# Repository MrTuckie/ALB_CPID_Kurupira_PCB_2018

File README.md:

# Kurupira-PCB
Descrição da PCB e dos componentes na PCB

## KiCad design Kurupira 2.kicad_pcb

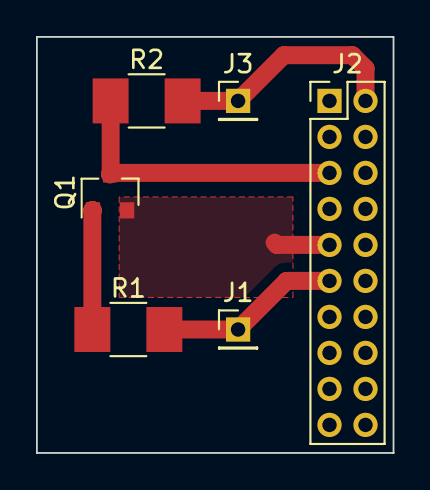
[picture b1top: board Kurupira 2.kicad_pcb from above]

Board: 2 copper layers, 19.8 x 23.1 mm, 6 parts (0 on the bottom side), 5 nets.

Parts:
J1, J3: Conn_01x01_Female; Pin_Header_Straight_1x01_Pitch2.00mm
J2: Conn_02x10_Odd_Even; Pin_Header_Straight_2x10_Pitch2.00mm
Q1: Q_NPN_BEC; SOT-23
R1, R2: R; R_1210_HandSoldering

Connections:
+5V: J2.2, J3.1, R2.2
GND: J2.9, Q1.2
unnamed: Q1.1, R1.1
PIR: J1.1, J2.11, R1.2
V_out: J2.5, Q1.3, R2.1

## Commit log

2018-09-08 adicionando os primeiros arquivos
2018-09-08 Testando no pc o novo email
2018-09-08 atualizando o email
2018-09-10 upando o mais atual
2018-09-10 aberto dps de upado
2018-10-05 teste
2018-10-19 Trocando os repositórios
2018-10-24 Gerber files + Coppercam pcb
    Adicionando os arquivos
2018-11-08 Mudando o pcb e as zonas
